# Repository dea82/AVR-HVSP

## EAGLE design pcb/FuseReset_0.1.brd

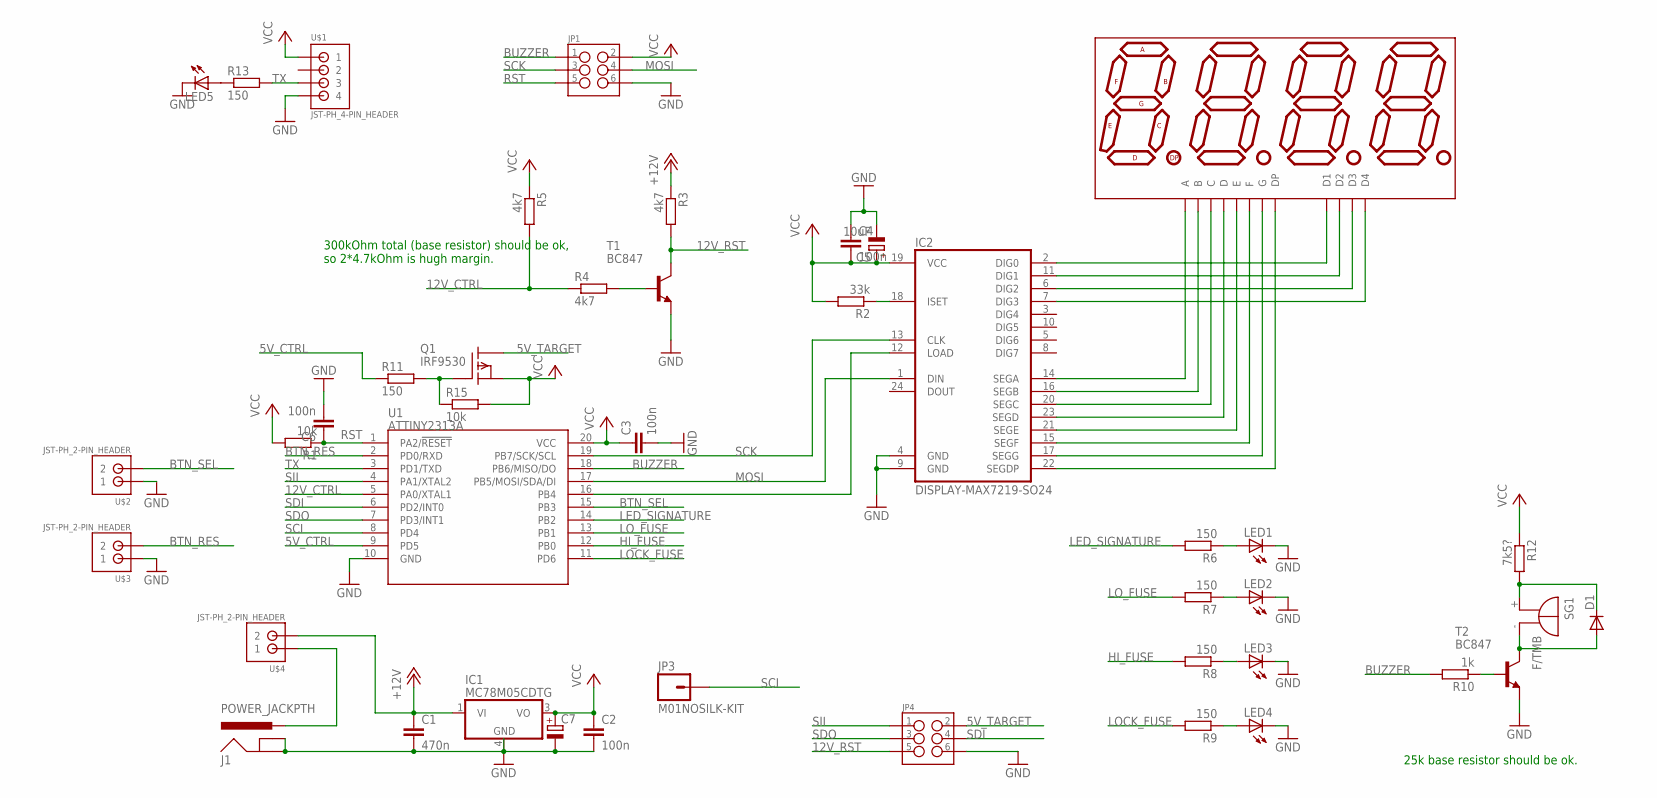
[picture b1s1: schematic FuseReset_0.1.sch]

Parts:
C1: 470n; C0805
C2, C3, C4, C6: 100n; C0805
C5: 10uF; 153CLV-0405
C7: CPOL-EUE2-5; E2-5
D1: DIODE-DO-214AC; DO-214AC
DISP2: 7-SEGMENT-4DIGIT-COUNTER; 7-SEGMENT-4DIGIT-COUNTER-0.36"
IC1: MC78M05CDTG; DPACK_3
IC2: DISPLAY-MAX7219-SO24; SO24L
J1: POWER_JACKPTH; POWER_JACK_PTH
JP1, JP4: M03X2SHROUD; 2X3-SHROUDED
JP3: M01NOSILK-KIT; 1X01NS-KIT
LED1, LED2, LED3, LED4: LED3MM
LED5: LED-0805; LED-805
Q1: IRF9530; TO220
R1, R15: 10k; R0805
R2: 33k; R0805
R3, R4, R5: 4k7; R0805
R6, R7, R8, R9, R11, R13: 150; R0805
R10: 1k; R0805
R12: 7k5?; R0805
SG1: F/TMB
T1, T2: BC847; SOT23
U1: ATTINY2313A; SOP20W
U$1: JST-PH_4-PIN_HEADER; JST_B4B-PH_HEADER
U$2, U$3, U$4: JST-PH_2-PIN_HEADER; JST_B2B-PH_HEADER

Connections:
5V_CTRL: R11.1, U1.9 (PD5)
5V_TARGET: JP4.2, Q1.2 (D)
12V_CTRL: R4.1, R5.2, U1.5 (PA0/XTAL1)
12V_RST: JP4.5, R3.2, T1.3 (C)
+12V: C1.1, IC1.1 (VI), R3.1, U$4.P2 (2)
BTN_RES: U1.2 (PD0/RXD), U$3.P2 (2)
BTN_SEL: U1.15 (PB3), U$2.P2 (2)
BUZZER: JP1.1, R10.2, U1.18 (PB6/MISO/DO)
GND: C1.2, C2.2, C3.2, C4.1, C5.-, C6.2, C7.-, IC1.4 (GND), IC2.4 (GND), IC2.9 (GND), J1.GND, J1.GNDBREAK, JP1.6, JP4.6, LED1.K (C), LED2.K (C), LED3.K (C), LED4.K (C), LED5.C, T1.2 (E), T2.2 (E), U1.10 (GND), U$1.P4 (4), U$2.P1 (1), U$3.P1 (1)
HI_FUSE: R8.2, U1.12 (PB0)
LED_SIGNATURE: R6.2, U1.14 (PB2)
LOCK_FUSE: R9.2, U1.11 (PD6)
LO_FUSE: R7.2, U1.13 (PB1)
MOSI: IC2.1 (DIN), JP1.4, U1.17 (PB5/MOSI/SDA/DI)
unnamed: DISP2.12 (D1), IC2.2 (DIG0)
unnamed: DISP2.9 (D2), IC2.11 (DIG1)
unnamed: DISP2.8 (D3), IC2.6 (DIG2)
unnamed: DISP2.6 (D4), IC2.7 (DIG3)
unnamed: DISP2.11 (A), IC2.14 (SEGA)
unnamed: DISP2.7 (B), IC2.16 (SEGB)
unnamed: DISP2.4 (C), IC2.20 (SEGC)
unnamed: DISP2.2 (D), IC2.23 (SEGD)
unnamed: DISP2.1 (E), IC2.21 (SEGE)
unnamed: DISP2.10 (F), IC2.15 (SEGF)
unnamed: DISP2.5 (G), IC2.17 (SEGG)
unnamed: DISP2.3 (DP), IC2.22 (SEGDP)
unnamed: IC2.18 (ISET), R2.1
unnamed: LED3.A, R8.1
unnamed: LED4.A, R9.1
unnamed: J1.PWR, U$4.P1 (1)
unnamed: LED2.A, R7.1
unnamed: LED1.A, R6.1
unnamed: R4.2, T1.1 (B)
unnamed: IC2.12 (LOAD), U1.16 (PB4)
unnamed: R10.1, T2.1 (B)
unnamed: LED5.A, R13.1
unnamed: D1.2 (A), SG1.-, T2.3 (C)
unnamed: D1.1 (C), R12.2, SG1.+
unnamed: Q1.1 (G), R11.2, R15.1
RST: C6.1, JP1.5, R1.1, U1.1 (PA2/!RESET)
SCI: JP3.1, U1.8 (PD4)
SCK: IC2.13 (CLK), JP1.3, U1.19 (PB7/SCK/SCL)
SDI: JP4.4, U1.6 (PD2/INT0)
SDO: JP4.3, U1.7 (PD3/INT1)
SII: JP4.1, U1.4 (PA1/XTAL2)
TX: R13.2, U1.3 (PD1/TXD), U$1.P3 (3)
VCC: C2.1, C3.1, C4.2, C5.+, C7.+, IC1.3 (VO), IC2.19 (VCC), JP1.2, Q1.3 (S), R1.2, R2.2, R5.1, R12.1, R15.2, U1.20 (VCC), U$1.P1 (1)

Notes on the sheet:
300kOhm total (base resistor) should be ok, so 2*4.7kOhm is hugh margin.
25k base resistor should be ok.

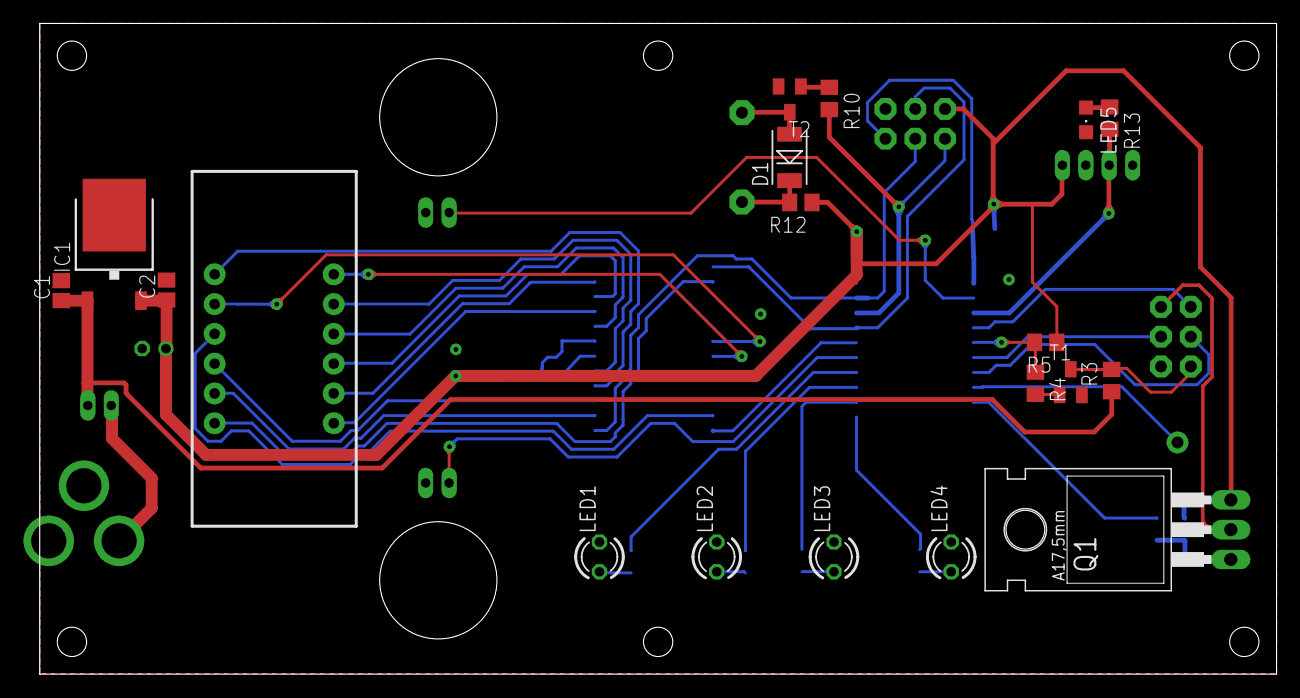
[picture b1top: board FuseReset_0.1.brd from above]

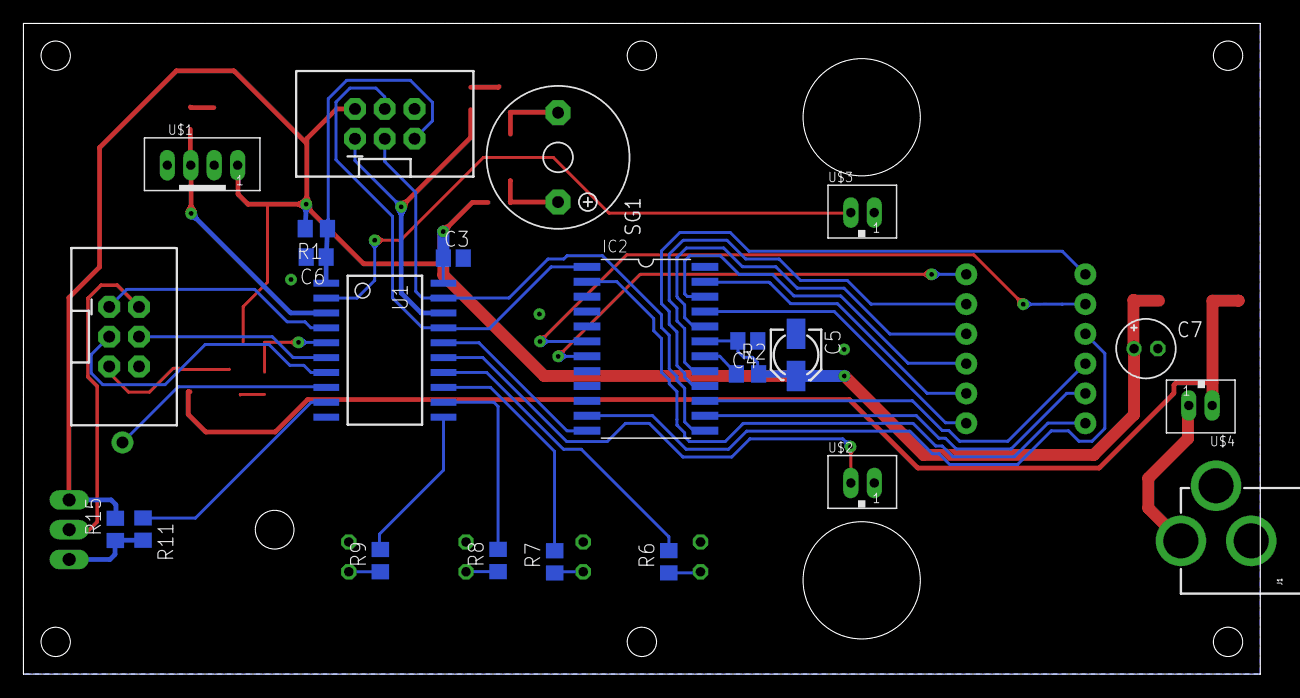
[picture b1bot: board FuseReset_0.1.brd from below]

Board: 2 copper layers, 105.5 x 55.5 mm, 43 parts (24 on the bottom side), 47 nets.

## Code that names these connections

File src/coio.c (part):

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 The following algorithm puts the device in High-voltage Serial Programming mode:
 (see Atmel ATtiny data sheet chapter Memory Programming -> High Voltage Serial Programming)

 1. Set Prog_enable pins (SDI, SII, SDO, SCI) 0, RESET pin and VCC to 0V.
 2. Apply 5V between VCC and GND. Ensure that VCC reaches at least 1.8V within the next 20 microseconds.
 3. Wait 20 - 60 us, and apply 11.5 - 12.5V to RESET.
 4. Keep the Prog_enable pins unchanged for at least 10 us after the High-voltage has been
 applied to ensure the Prog_enable Signature has been latched.
 5. Release the Prog_enable[2] (SDO pin) to avoid drive contention on the Prog_enable[2]/SDO pin.
 6. Wait at least 300 us before giving any serial instructions on SDI/SII.
 7. Exit Programming mode by power the device down or by bringing RESET pin to 0V.
 */
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
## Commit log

2015-06-24 Added PCB layout.
2015-06-24 Ignore temples created by Eagle.
2015-07-10 Updates on PCB-design.
2015-07-10 Small cosmetic change.
2015-07-11 Initial src commit.
2015-07-17 Display with MAX7219 and 4-digit led is working.
2015-07-27 Huge update. Able to communicate with target device.
2015-08-04 Everything seems to work now. Read chip, print device name, fuses etc. Reset also works.
2015-08-04 Cleared unused enum.
2015-11-11 Create Makefile
2015-11-11 Update Makefile
2016-01-28 no message
2016-05-10 Optimization of makefile to save som flash

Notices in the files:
parts and their libraries:
SparkFun-Connectors: Licensing: Creative Commons ShareAlike 4.0 International - https://creativecommons.org/licenses/by-sa/4.0
